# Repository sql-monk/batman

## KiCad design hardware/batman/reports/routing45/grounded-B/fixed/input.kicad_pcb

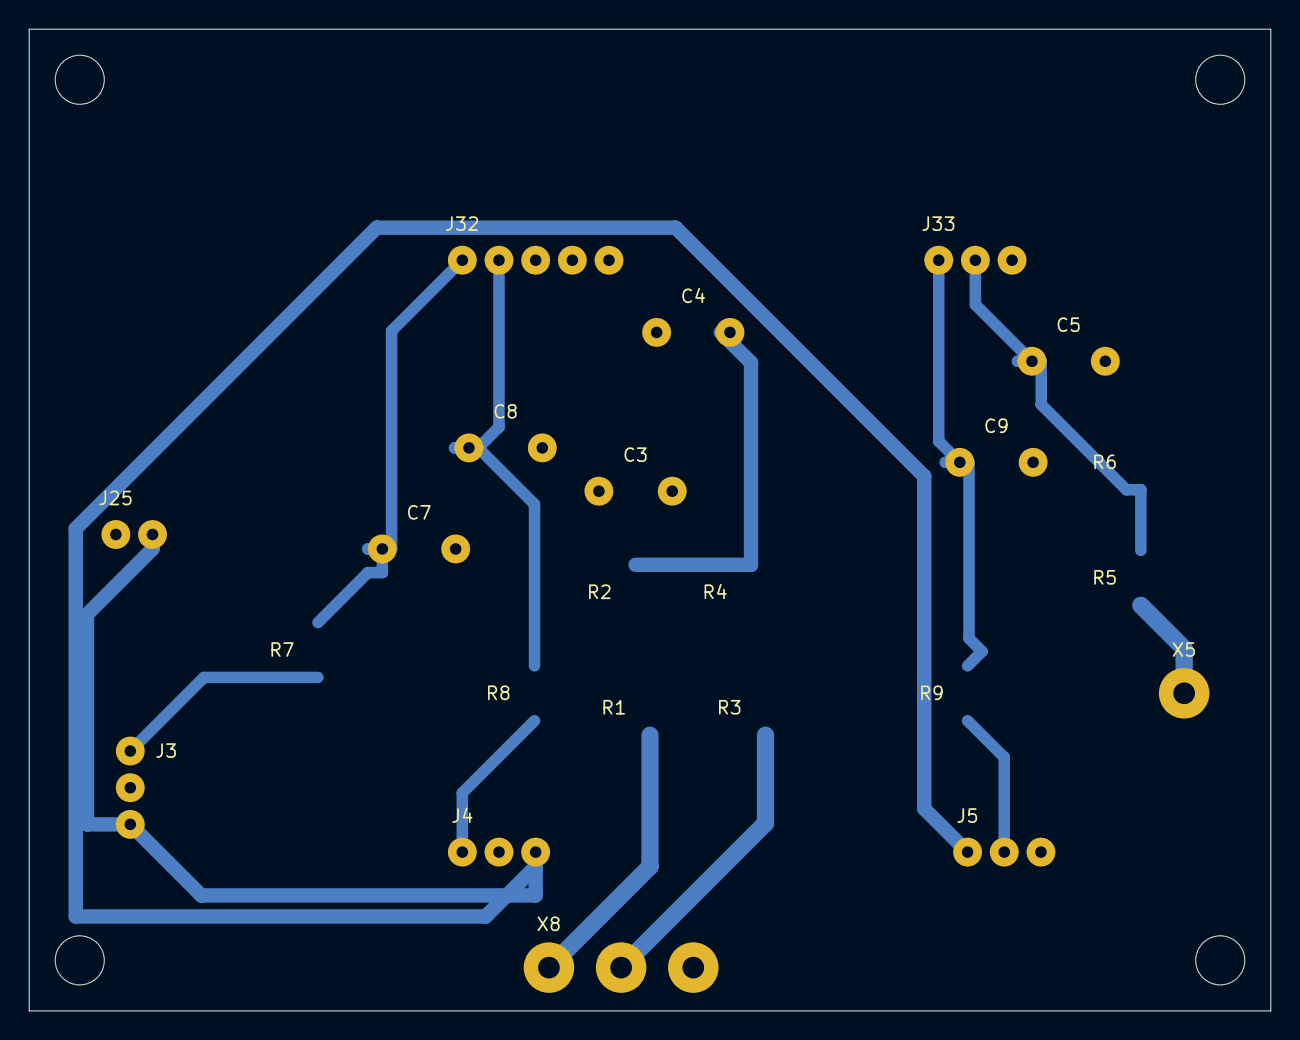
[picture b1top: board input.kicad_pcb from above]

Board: 2 copper layers, 86.0 x 68.0 mm, 27 parts (0 on the bottom side), 14 nets.

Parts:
C3: 100n_50V; LUT_C3
C4: 100n_50V; LUT_C4
C5: 100n_50V; LUT_C5
C7: 1u_16V; LUT_C7
C8: 1u_16V; LUT_C8
C9: 1u_16V; LUT_C9
HB1, HB2, HB3, HB4: M3_NPTH_3.4; Mount_M3
J3: ACS1_3WIRE; LUT_J3
J4: ACS2_3WIRE; LUT_J4
J5: ACS3_3WIRE; LUT_J5
J25: LINK_GND_+3V3_SENS; LUT_J25
J32: LINK_I_B1_I_B2_U_B1_U_B2_GND; LUT_J32
J33: LINK_I_LOAD_U_LOAD_GND; LUT_J33
R1: 100k_1%; LUT_R1
R2: 10k_1%; LUT_R2
R3: 100k_1%; LUT_R3
R4: 10k_1%; LUT_R4
R5: 100k_1%; LUT_R5
R6: 4.7k_1%; LUT_R6
R7: 1k; LUT_R7
R8: 1k; LUT_R8
R9: 1k; LUT_R9
X5: U_LOAD_SENSE; LUT_X5
X8: BAT_SENSE_FROM_D; LUT_X8

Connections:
+3V3_SENS: J3.3, J4.3, J5.1, J25.2
B1: R1.1, X8.1
B2: R3.1, X8.2
GND: C3.2, C4.2, C5.2, C7.2, C8.2, C9.2, J3.2, J4.2, J5.3, J25.1, J32.5, J33.3, R2.2, R4.2, R6.2, X8.3
I_B1: C7.1, J32.1, R7.2
I_B2: C8.1, J32.2, R8.2
I_LOAD: C9.1, J33.1, R9.2
I_RAW1: J3.1, R7.1
I_RAW2: J4.1, R8.1
I_RAW3: J5.2, R9.1
LOAD+: R5.1, X5.1
U_B1: C3.1, J32.3, R1.2, R2.1
U_B2: C4.1, J32.4, R3.2, R4.1
U_LOAD: C5.1, J33.2, R5.2, R6.1

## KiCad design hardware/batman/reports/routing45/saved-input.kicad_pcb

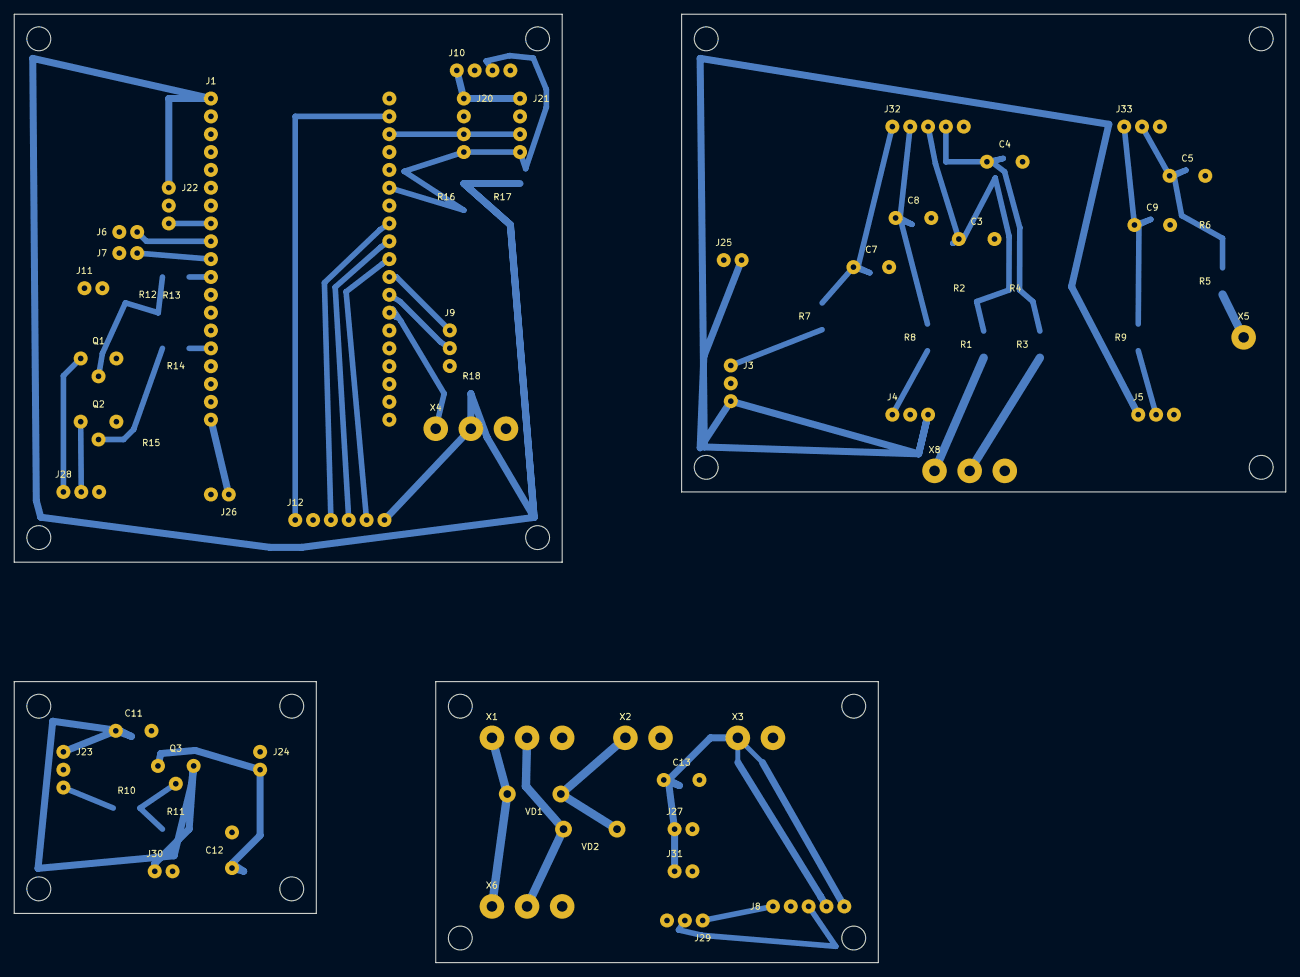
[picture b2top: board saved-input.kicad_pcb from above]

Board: 2 copper layers, 181.0 x 135.0 mm, 98 parts (0 on the bottom side), 39 nets.

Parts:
C3: 100n_50V; LUT_C3
C4: 100n_50V; LUT_C4
C5: 100n_50V; LUT_C5
C7: 1u_16V; LUT_C7
C8: 1u_16V; LUT_C8
C9: 1u_16V; LUT_C9
C11: 100n_16V; LUT_C11
C12: 100n_16V; LUT_C12
C13: 100n_16V; LUT_C13
HA1, HA2, HA3, HA4: M3_NPTH_3.4; Mount_M3
HB1, HB2, HB3, HB4: M3_NPTH_3.4; Mount_M3
HC1, HC2, HC3, HC4: M3_NPTH_3.4; Mount_M3
HD1, HD2, HD3, HD4: M3_NPTH_3.4; Mount_M3
J1: DevKitC_38_socket_mMCU; LUT_J1
J3: ACS1_3WIRE; LUT_J3
J4: ACS2_3WIRE; LUT_J4
J5: ACS3_3WIRE; LUT_J5
J6: SW1_GND_ON; LUT_J6
J7: SW2_GND_ON; LUT_J7
J8: RELAY; LUT_J8
J9: DPS_UART; LUT_J9
J10: OLED_I2C; LUT_J10
J11: BUTTON; LUT_J11
J12: SPI; LUT_J12
J20: LINK_+3V3_GND_SCL_SDA; LUT_J20
J21: LINK_+3V3_GND_SCL_SDA; LUT_J21
J22: LINK_+3V3_GND_SENS_PWR; LUT_J22
J23: LINK_+3V3_GND_SENS_PWR; LUT_J23
J24: LINK_GND_+3V3_SENS; LUT_J24
J25: LINK_GND_+3V3_SENS; LUT_J25
J26: LINK_+5V_GND; LUT_J26
J27: LINK_+5V_GND; LUT_J27
J28: LINK_RELAY_IN1_RELAY_IN2_GND; LUT_J28
J29: LINK_RELAY_IN1_RELAY_IN2_GND; LUT_J29
J30: LINK_+3V3_GND; LUT_J30
J31: LINK_+5V_GND; LUT_J31
J32: LINK_I_B1_I_B2_U_B1_U_B2_GND; LUT_J32
J33: LINK_I_LOAD_U_LOAD_GND; LUT_J33
NT1: COPPER_STAR_AT_X3; LUT_NT1
Q1: BC547_CBE; LUT_Q1
Q2: BC547_CBE; LUT_Q2
Q3: BC557_CBE; LUT_Q3
R1: 100k_1%; LUT_R1
R2: 10k_1%; LUT_R2
R3: 100k_1%; LUT_R3
R4: 10k_1%; LUT_R4
R5: 100k_1%; LUT_R5
R6: 4.7k_1%; LUT_R6
R7: 1k; LUT_R7
R8: 1k; LUT_R8
R9: 1k; LUT_R9
R10: 4.7k; LUT_R10
R11: 10k; LUT_R11
R12: 1k; LUT_R12
R13: 10k; LUT_R13
R14: 1k; LUT_R14
R15: 10k; LUT_R15
R16: 4.7k; LUT_R16
R17: 4.7k; LUT_R17
R18: 4.7k; LUT_R18
VD1: 1N5819; LUT_VD1
VD2: 1N5819; LUT_VD2
WA1: INSULATED_WIRE; LUT_WA1
WA2: INSULATED_WIRE; LUT_WA2
WA3: INSULATED_WIRE; LUT_WA3
WA4: INSULATED_WIRE; LUT_WA4
WC2_1: EXTERNAL_CABLE_NOT_PCB; LUT_WC2_1
WC2_2: EXTERNAL_CABLE_NOT_PCB; LUT_WC2_2
WC2_3: EXTERNAL_CABLE_NOT_PCB; LUT_WC2_3
WC3_1: EXTERNAL_CABLE_NOT_PCB; LUT_WC3_1
WC3_2: EXTERNAL_CABLE_NOT_PCB; LUT_WC3_2
WC4_1: EXTERNAL_CABLE_NOT_PCB; LUT_WC4_1
WC4_2: EXTERNAL_CABLE_NOT_PCB; LUT_WC4_2
WC5_1: EXTERNAL_CABLE_NOT_PCB; LUT_WC5_1
WC5_2: EXTERNAL_CABLE_NOT_PCB; LUT_WC5_2
WC5_3: EXTERNAL_CABLE_NOT_PCB; LUT_WC5_3
WC6_1: EXTERNAL_CABLE_NOT_PCB; LUT_WC6_1
WC6_2: EXTERNAL_CABLE_NOT_PCB; LUT_WC6_2
WC6_3: EXTERNAL_CABLE_NOT_PCB; LUT_WC6_3
X1: B1_B2_GND; LUT_X1
X2: VIN_DC_GND; LUT_X2
X3: 5V_GND; LUT_X3
X4: DS18B20; LUT_X4
X5: U_LOAD_SENSE; LUT_X5
X6: BAT_SENSE_TO_B; LUT_X6
X8: BAT_SENSE_FROM_D; LUT_X8

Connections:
+3V3: C11.1, J1.1, J10.1, J12.6, J20.1, J21.1, J22.1, J23.1, J30.1, Q3.3, R11.2, R16.2, R17.2, R18.2, WA1.1, WC2_1.1, X4.2
+3V3_SENS: C12.1, J3.3, J4.3, J5.1, J24.2, J25.2, Q3.1, WC3_2.1
+5V: C13.1, J1.19, J26.1, J27.1, J31.1, NT1.1, WC4_1.1, X3.1
+5V_RELAY_COIL: J8.5, NT1.3
+5V_RELAY_VCC: J8.4, NT1.2
B1: R1.1, VD1.2, WC6_1.1, X1.1, X6.1, X8.1
B2: R3.1, VD2.2, WC6_2.1, X1.2, X6.2, X8.2
BASE1: Q1.2, R12.2, R13.1
BASE2: Q2.2, R14.2, R15.1
BASE3: Q3.2, R10.2, R11.1
BTN: J1.7, J11.2, WA2.1
CS: J1.29, J12.5
DPS_RX: J1.31, J9.2
DPS_TX: J1.30, J9.1
GND: C3.2, C4.2, C5.2, C7.2, C8.2, C9.2, C11.2, C12.2, C13.2, J1.14, J1.20, J1.26, J3.2, J4.2, J5.3, J6.1, J7.1, J8.2, J9.3, J10.4, J11.1, J12.2, J20.2, J21.2, J22.2, J23.2, J24.1, J25.1, J26.2, J27.2, J28.3, J29.3, J30.2, J31.2, J32.5, J33.3, Q1.3, Q2.3, R2.2, R4.2, R6.2, R13.2, R15.2, WC2_2.1, WC3_1.1, WC4_2.1, WC5_3.1, WC6_3.1, X1.3, X2.2, X3.2, X4.3, X6.3, X8.3
I_B1: C7.1, J32.1, R7.2
I_B2: C8.1, J32.2, R8.2
I_LOAD: C9.1, J33.1, R9.2
I_RAW1: J3.1, R7.1
I_RAW2: J4.1, R8.1
I_RAW3: J5.2, R9.1
K1: J1.11, R12.1
K2: J1.15, R14.1
LOAD+: R5.1, X5.1
MISO: J1.27, J12.3
MOSI: J1.21, J12.1
OW: J1.32, R18.1, X4.1
RELAY_IN1: J8.1, J28.1, J29.1, Q1.1, WC5_1.1
RELAY_IN2: J8.3, J28.2, J29.2, Q2.1, WC5_2.1
SCK: J1.28, J12.4
SCL: J1.22, J10.2, J20.3, J21.3, R17.1, WA3.1, WA4.1
SDA: J1.25, J10.3, J20.4, J21.4, R16.1
SENS_PWR: J1.8, J22.3, J23.3, R10.1, WC2_3.1
SW1_ON: J1.9, J6.2
SW2_ON: J1.10, J7.2
U_B1: C3.1, J32.3, R1.2, R2.1
U_B2: C4.1, J32.4, R3.2, R4.1
U_LOAD: C5.1, J33.2, R5.2, R6.1
VIN_DC: VD1.1, VD2.1, X2.1

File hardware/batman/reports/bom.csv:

Reference,Documentation_alias,Value,Quantity,Location,Populate
J1,,DevKitC_38_socket_mMCU,1,A,yes
J2,,ADS1115_socket_mADC,1,A,yes
J3,,ACS1_3WIRE,1,A,yes
J4,,ACS2_3WIRE,1,A,yes
J5,,ACS3_3WIRE,1,A,yes
J6,,SW1_GND_ON,1,A,yes
J7,,SW2_GND_ON,1,A,yes
J8,,RELAY,1,A,yes
J9,,DPS_UART,1,A,yes
J10,,OLED_I2C,1,A,yes
J11,,BUTTON,1,A,yes
J12,,SPI,1,A,yes
X1,,B1_B2_GND,1,A,yes
X2,,VIN_DC_GND,1,A,yes
X3,,5V_GND,1,A,yes
X4,,DS18B20,1,A,yes
X5,,U_LOAD_SENSE,1,A,yes
NT1,,COPPER_STAR_AT_X3,1,A,copper only
VD1,,1N5819,1,A,yes
VD2,,1N5819,1,A,yes
R1,,100k_1%,1,A,yes
R2,,10k_1%,1,A,yes
C3,,100n_50V,1,A,yes
R3,,100k_1%,1,A,yes
R4,,10k_1%,1,A,yes
C4,,100n_50V,1,A,yes
R5,,100k_1%,1,A,yes
R6,,4.7k_1%,1,A,yes
C5,,100n_50V,1,A,yes
R7,,1k,1,A,yes
C7,,1u_16V,1,A,yes
R8,,1k,1,A,yes
C8,,1u_16V,1,A,yes
R9,,1k,1,A,yes
C9,,1u_16V,1,A,yes
C6,,100n_16V,1,A,yes
R10,,4.7k,1,A,yes
R11,,10k,1,A,yes
Q3,,BC557_CBE,1,A,yes
R12,,1k,1,A,yes
R13,,10k,1,A,yes
Q1,,BC547_CBE,1,A,yes
R14,,1k,1,A,yes
R15,,10k,1,A,yes
Q2,,BC547_CBE,1,A,yes
R16,,4.7k,1,A,yes
R17,,4.7k,1,A,yes
R18,,4.7k,1,A,yes
XLP1,XLP,LOAD_P06_P12_P13,1,external,yes
XGND1,XGND,GND_P24_P25_P26_P27_P28,1,external,yes
C1,,100u_50V_ALUMINIUM,1,external,yes
C2,,100n_50V,1,external,yes
D3,,1.5KE33A_DNP,1,external,DNP
XB1,,BAT1_PANEL,1,external,yes
F1,,ATO_15A,1,external,yes
mACS1,,ACS711EX_15.5A,1,external,yes
mSW1,,Pololu_2815_HP,1,external,yes
mDIO1,,XL74610,1,external,yes
XB2,,BAT2_PANEL,1,external,yes
F2,,ATO_15A,1,external,yes
mACS2,,ACS711EX_15.5A,1,external,yes
mSW2,,Pololu_2815_HP,1,external,yes
mDIO2,,XL74610,1,external,yes
mACS3,,ACS711EX_15.5A,1,external,yes
Fout1,Fout,ATO_15A,1,external,yes
XLOAD1,XLOAD,LOAD_PANEL,1,external,yes
XPSU1,XPSU,PSU_33V_10A_PANEL,1,external,yes
mDPS1,mDPS,DPS5015_9600_8N1_ADDR1,1,external,yes
Fchg1,Fchg,ATO_15A,1,external,yes
mDIO3,,XL74610,1,external,yes
mREL2,,FL_3FF_5V_10A_REMOVE_JUMPER,1,external,yes
mDC5,,LM2596_SET_5.0V_FIRST,1,external,yes
mOLED1,mOLED,SSD1306_0x3C,1,external,yes
T1,,DS18B20_PROBE,1,external,yes
T2,,DS18B20_PROBE,1,external,yes
SW1,,PANEL_BUTTON_NO,1,external,yes

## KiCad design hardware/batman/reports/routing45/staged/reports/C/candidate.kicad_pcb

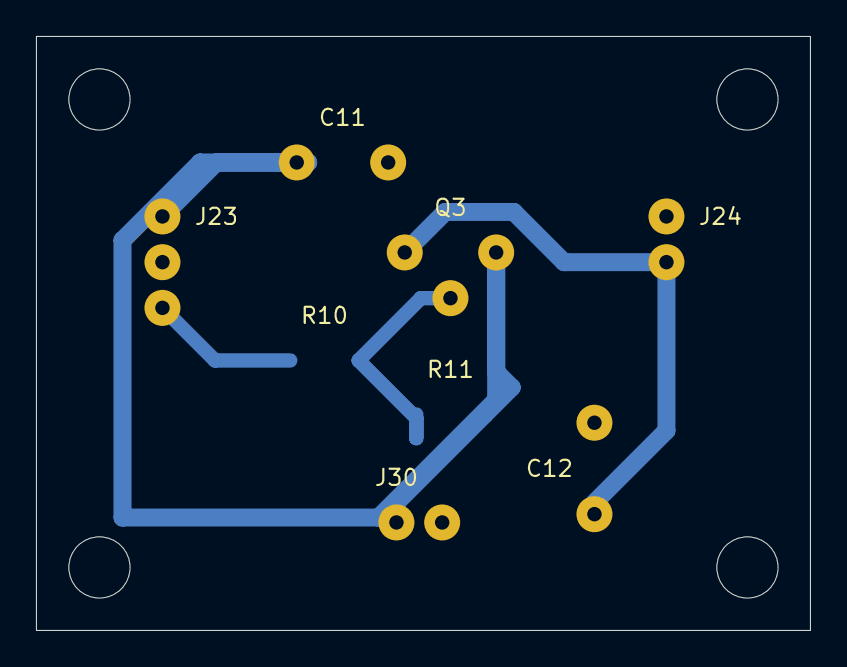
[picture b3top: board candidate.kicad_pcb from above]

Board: 2 copper layers, 43.0 x 33.0 mm, 12 parts (0 on the bottom side), 5 nets.

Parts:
C11: 100n_16V; LUT_C11
C12: 100n_16V; LUT_C12
HC1, HC2, HC3, HC4: M3_NPTH_3.4; Mount_M3
J23: LINK_+3V3_GND_SENS_PWR; LUT_J23
J24: LINK_GND_+3V3_SENS; LUT_J24
J30: LINK_+3V3_GND; LUT_J30
Q3: BC557_CBE; LUT_Q3
R10: 4.7k; LUT_R10
R11: 10k; LUT_R11

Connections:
+3V3: C11.1, J23.1, J30.1, Q3.3, R11.2
+3V3_SENS: C12.1, J24.2, Q3.1
BASE3: Q3.2, R10.2, R11.1
GND: C11.2, C12.2, J23.2, J24.1, J30.2
SENS_PWR: J23.3, R10.1

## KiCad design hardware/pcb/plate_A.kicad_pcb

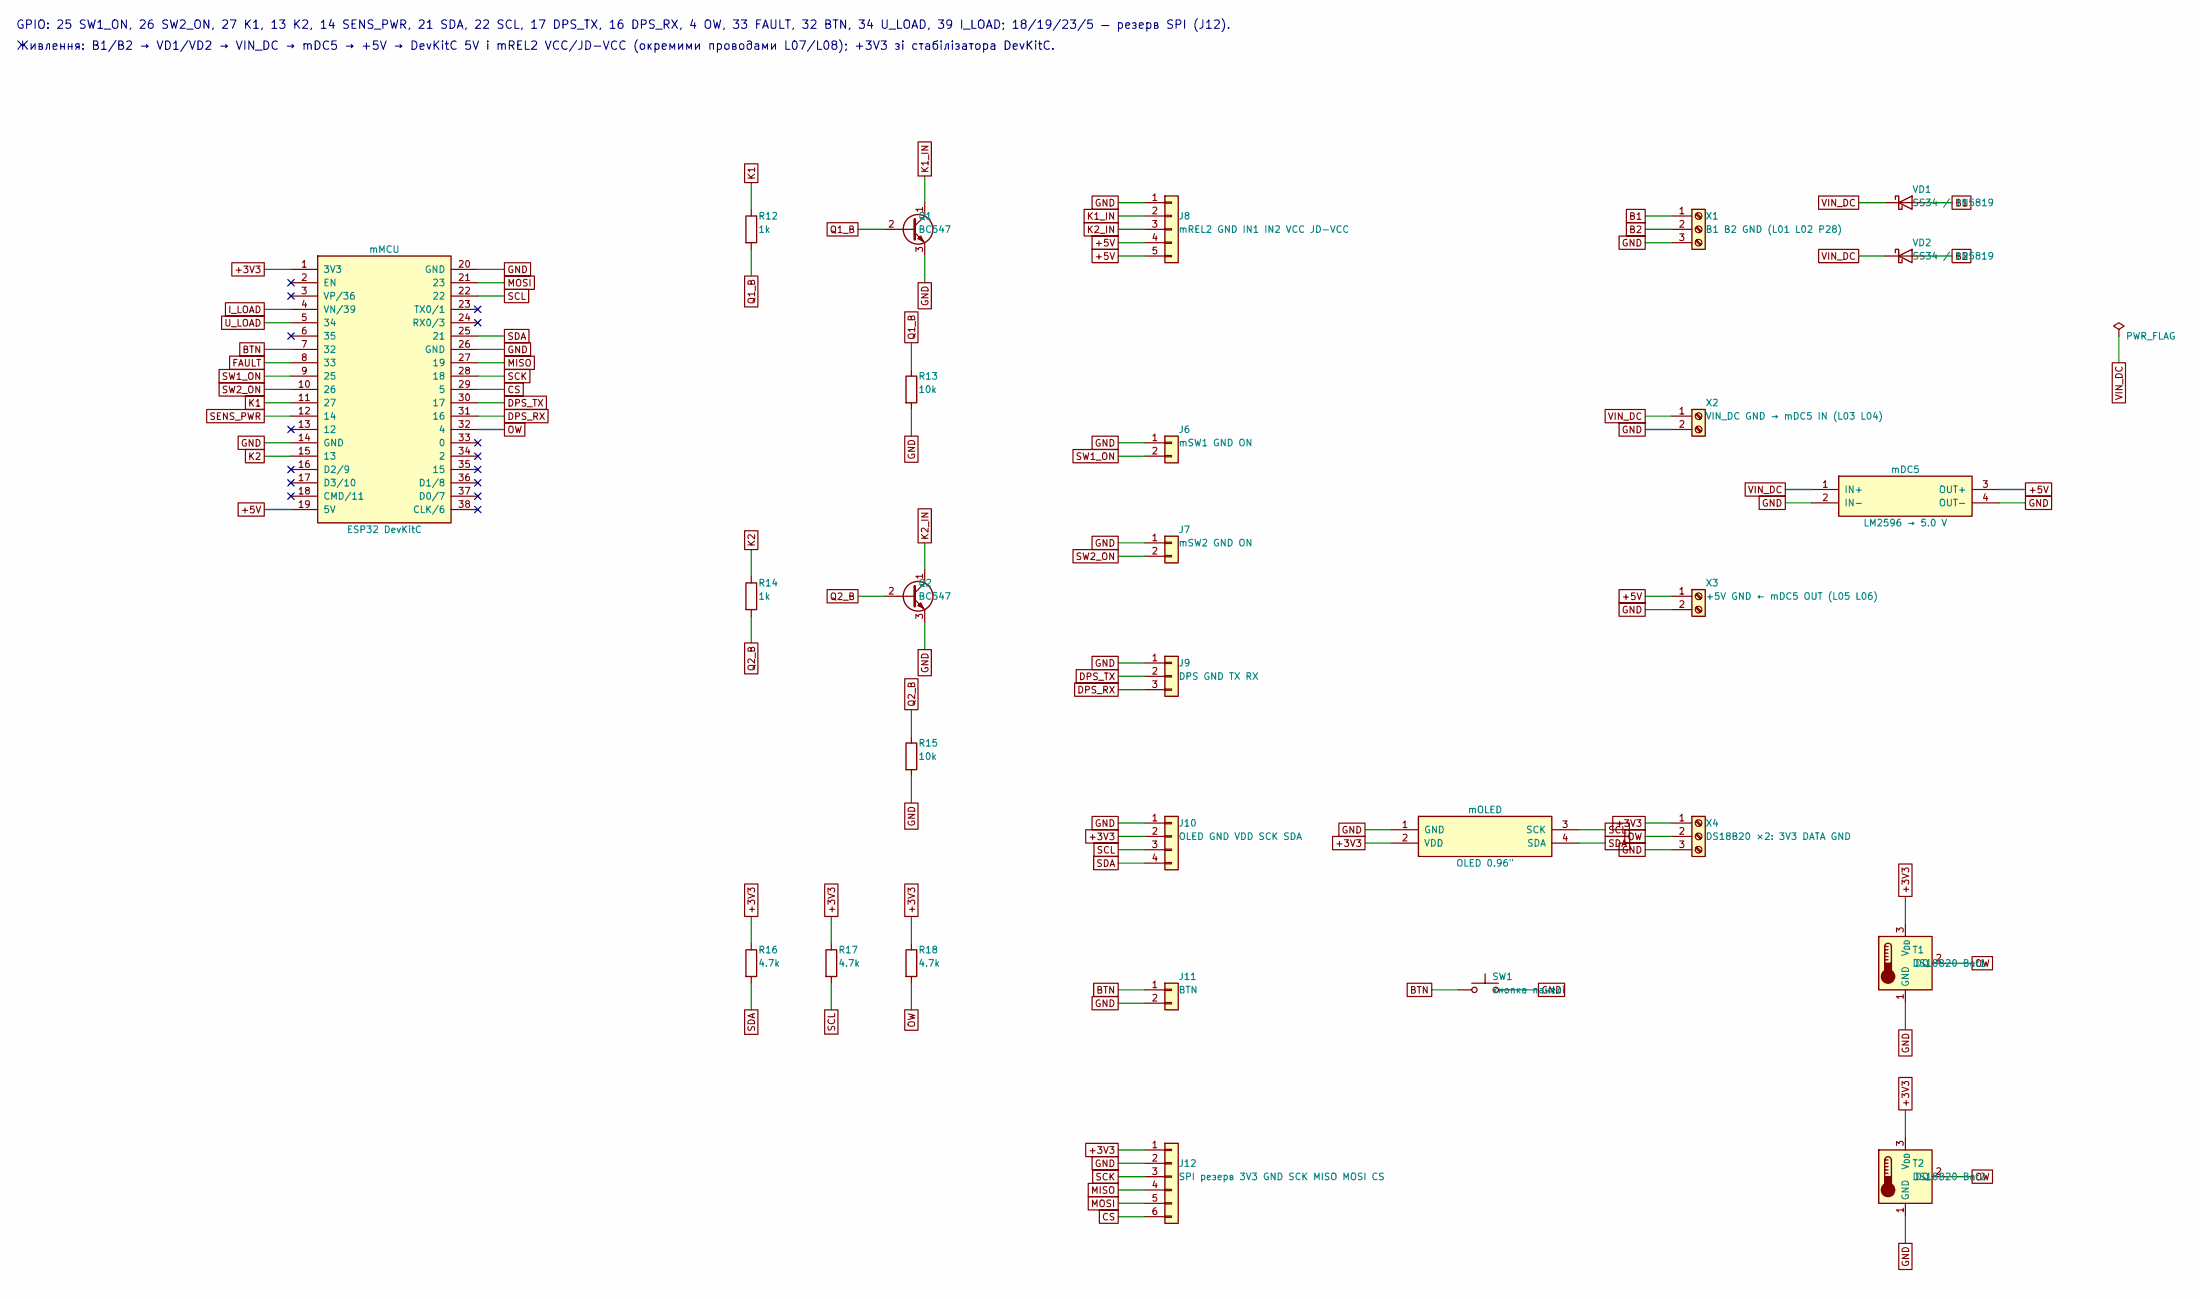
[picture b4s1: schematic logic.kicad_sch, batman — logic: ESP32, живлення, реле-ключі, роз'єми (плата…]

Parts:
J6: mSW1 GND ON; PinHeader_1x02_P2.54mm_Vertical
J7: mSW2 GND ON; PinHeader_1x02_P2.54mm_Vertical
J8: mREL2 GND IN1 IN2 VCC JD-VCC; PinHeader_1x05_P2.54mm_Vertical
J9: DPS GND TX RX; PinHeader_1x03_P2.54mm_Vertical
J10: OLED GND VDD SCK SDA; PinHeader_1x04_P2.54mm_Vertical
J11: BTN; PinHeader_1x02_P2.54mm_Vertical
J12: SPI резерв 3V3 GND SCK MISO MOSI CS; PinHeader_1x06_P2.54mm_Vertical
Q1, Q2: BC547; TO-92_Inline
R12, R14: 1k; R_1206_3216Metric
R13, R15: 10k; R_1206_3216Metric
R16, R17, R18: 4.7k; R_1206_3216Metric
SW1: кнопка панелі; SW_PUSH_6mm
T1: DS18B20 Bat1
T2: DS18B20 Bat2
VD1, VD2: SS34 / 1N5819; D_DO-41_SOD81_P10.16mm_Horizontal
X1: B1 B2 GND (L01 L02 P28); TerminalBlock_MaiXu_MX126-5.0-03P_1x03_P5.00mm
X2: VIN_DC GND → mDC5 IN (L03 L04); TerminalBlock_MaiXu_MX126-5.0-02P_1x02_P5.00mm
X3: +5V GND ← mDC5 OUT (L05 L06); TerminalBlock_MaiXu_MX126-5.0-02P_1x02_P5.00mm
X4: DS18B20 ×2: 3V3 DATA GND; TerminalBlock_MaiXu_MX126-5.0-03P_1x03_P5.00mm
mDC5: LM2596 → 5.0 V
mMCU: ESP32 DevKitC; ESP32_DevKitC_38_Socket
mOLED: OLED 0.96"

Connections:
+3V3: J10.2, J12.1, R16.1, R17.1, R18.1, T1.3 (V_{DD}), T2.3 (V_{DD}), X4.1, mMCU.1 (3V3), mOLED.2 (VDD); also elsewhere on the board
+5V: J8.4, J8.5, X3.1, mDC5.3 (OUT+), mMCU.19 (5V)
B1: VD1.2 (A), X1.1; also elsewhere on the board
B2: VD2.2 (A), X1.2; also elsewhere on the board
BTN: J11.1, SW1.1, mMCU.7 (32)
CS: J12.6, mMCU.29 (5)
DPS_RX: J9.3, mMCU.31 (16)
DPS_TX: J9.2, mMCU.30 (17)
FAULT: mMCU.8 (33); also elsewhere on the board
GND: J6.1, J7.1, J8.1, J9.1, J10.1, J11.2, J12.2, Q1.3 (E), Q2.3 (E), R13.2, R15.2, SW1.2, T1.1 (GND), T2.1 (GND), X1.3, X2.2, X3.2, X4.3, mDC5.2 (IN-), mDC5.4 (OUT-), mMCU.14 (GND), mMCU.20 (GND), mMCU.26 (GND), mOLED.1 (GND); also elsewhere on the board
I_LOAD: mMCU.4 (VN/39); also elsewhere on the board
K1: R12.1, mMCU.11 (27)
K1_IN: J8.2, Q1.1 (C)
K2: R14.1, mMCU.15 (13)
K2_IN: J8.3, Q2.1 (C)
MISO: J12.4, mMCU.27 (19)
MOSI: J12.5, mMCU.21 (23)
OW: R18.2, T1.2 (DQ), T2.2 (DQ), X4.2, mMCU.32 (4)
Q1_B: Q1.2 (B), R12.2, R13.1
Q2_B: Q2.2 (B), R14.2, R15.1
SCK: J12.3, mMCU.28 (18)
SCL: J10.3, R17.2, mMCU.22, mOLED.3 (SCK); also elsewhere on the board
SDA: J10.4, R16.2, mMCU.25 (21), mOLED.4 (SDA); also elsewhere on the board
SENS_PWR: mMCU.12 (14); also elsewhere on the board
SW1_ON: J6.2, mMCU.9 (25)
SW2_ON: J7.2, mMCU.10 (26)
U_LOAD: mMCU.5 (34); also elsewhere on the board
VIN_DC: VD1.1 (K), VD2.1 (K), X2.1, mDC5.1 (IN+)

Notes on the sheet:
GPIO: 25 SW1_ON, 26 SW2_ON, 27 K1, 13 K2, 14 SENS_PWR, 21 SDA, 22 SCL, 17 DPS_TX, 16 DPS_RX, 4 OW, 33 FAULT, 32 BTN, 34 U_LOAD, 39 I_LOAD; 18/19/23/5 — резерв SPI (J12).
Живлення: B1/B2 → VD1/VD2 → VIN_DC → mDC5 → +5V → DevKitC 5V і mREL2 VCC/JD-VCC (окремими проводами L07/L08); +3V3 зі стабілізатора DevKitC.

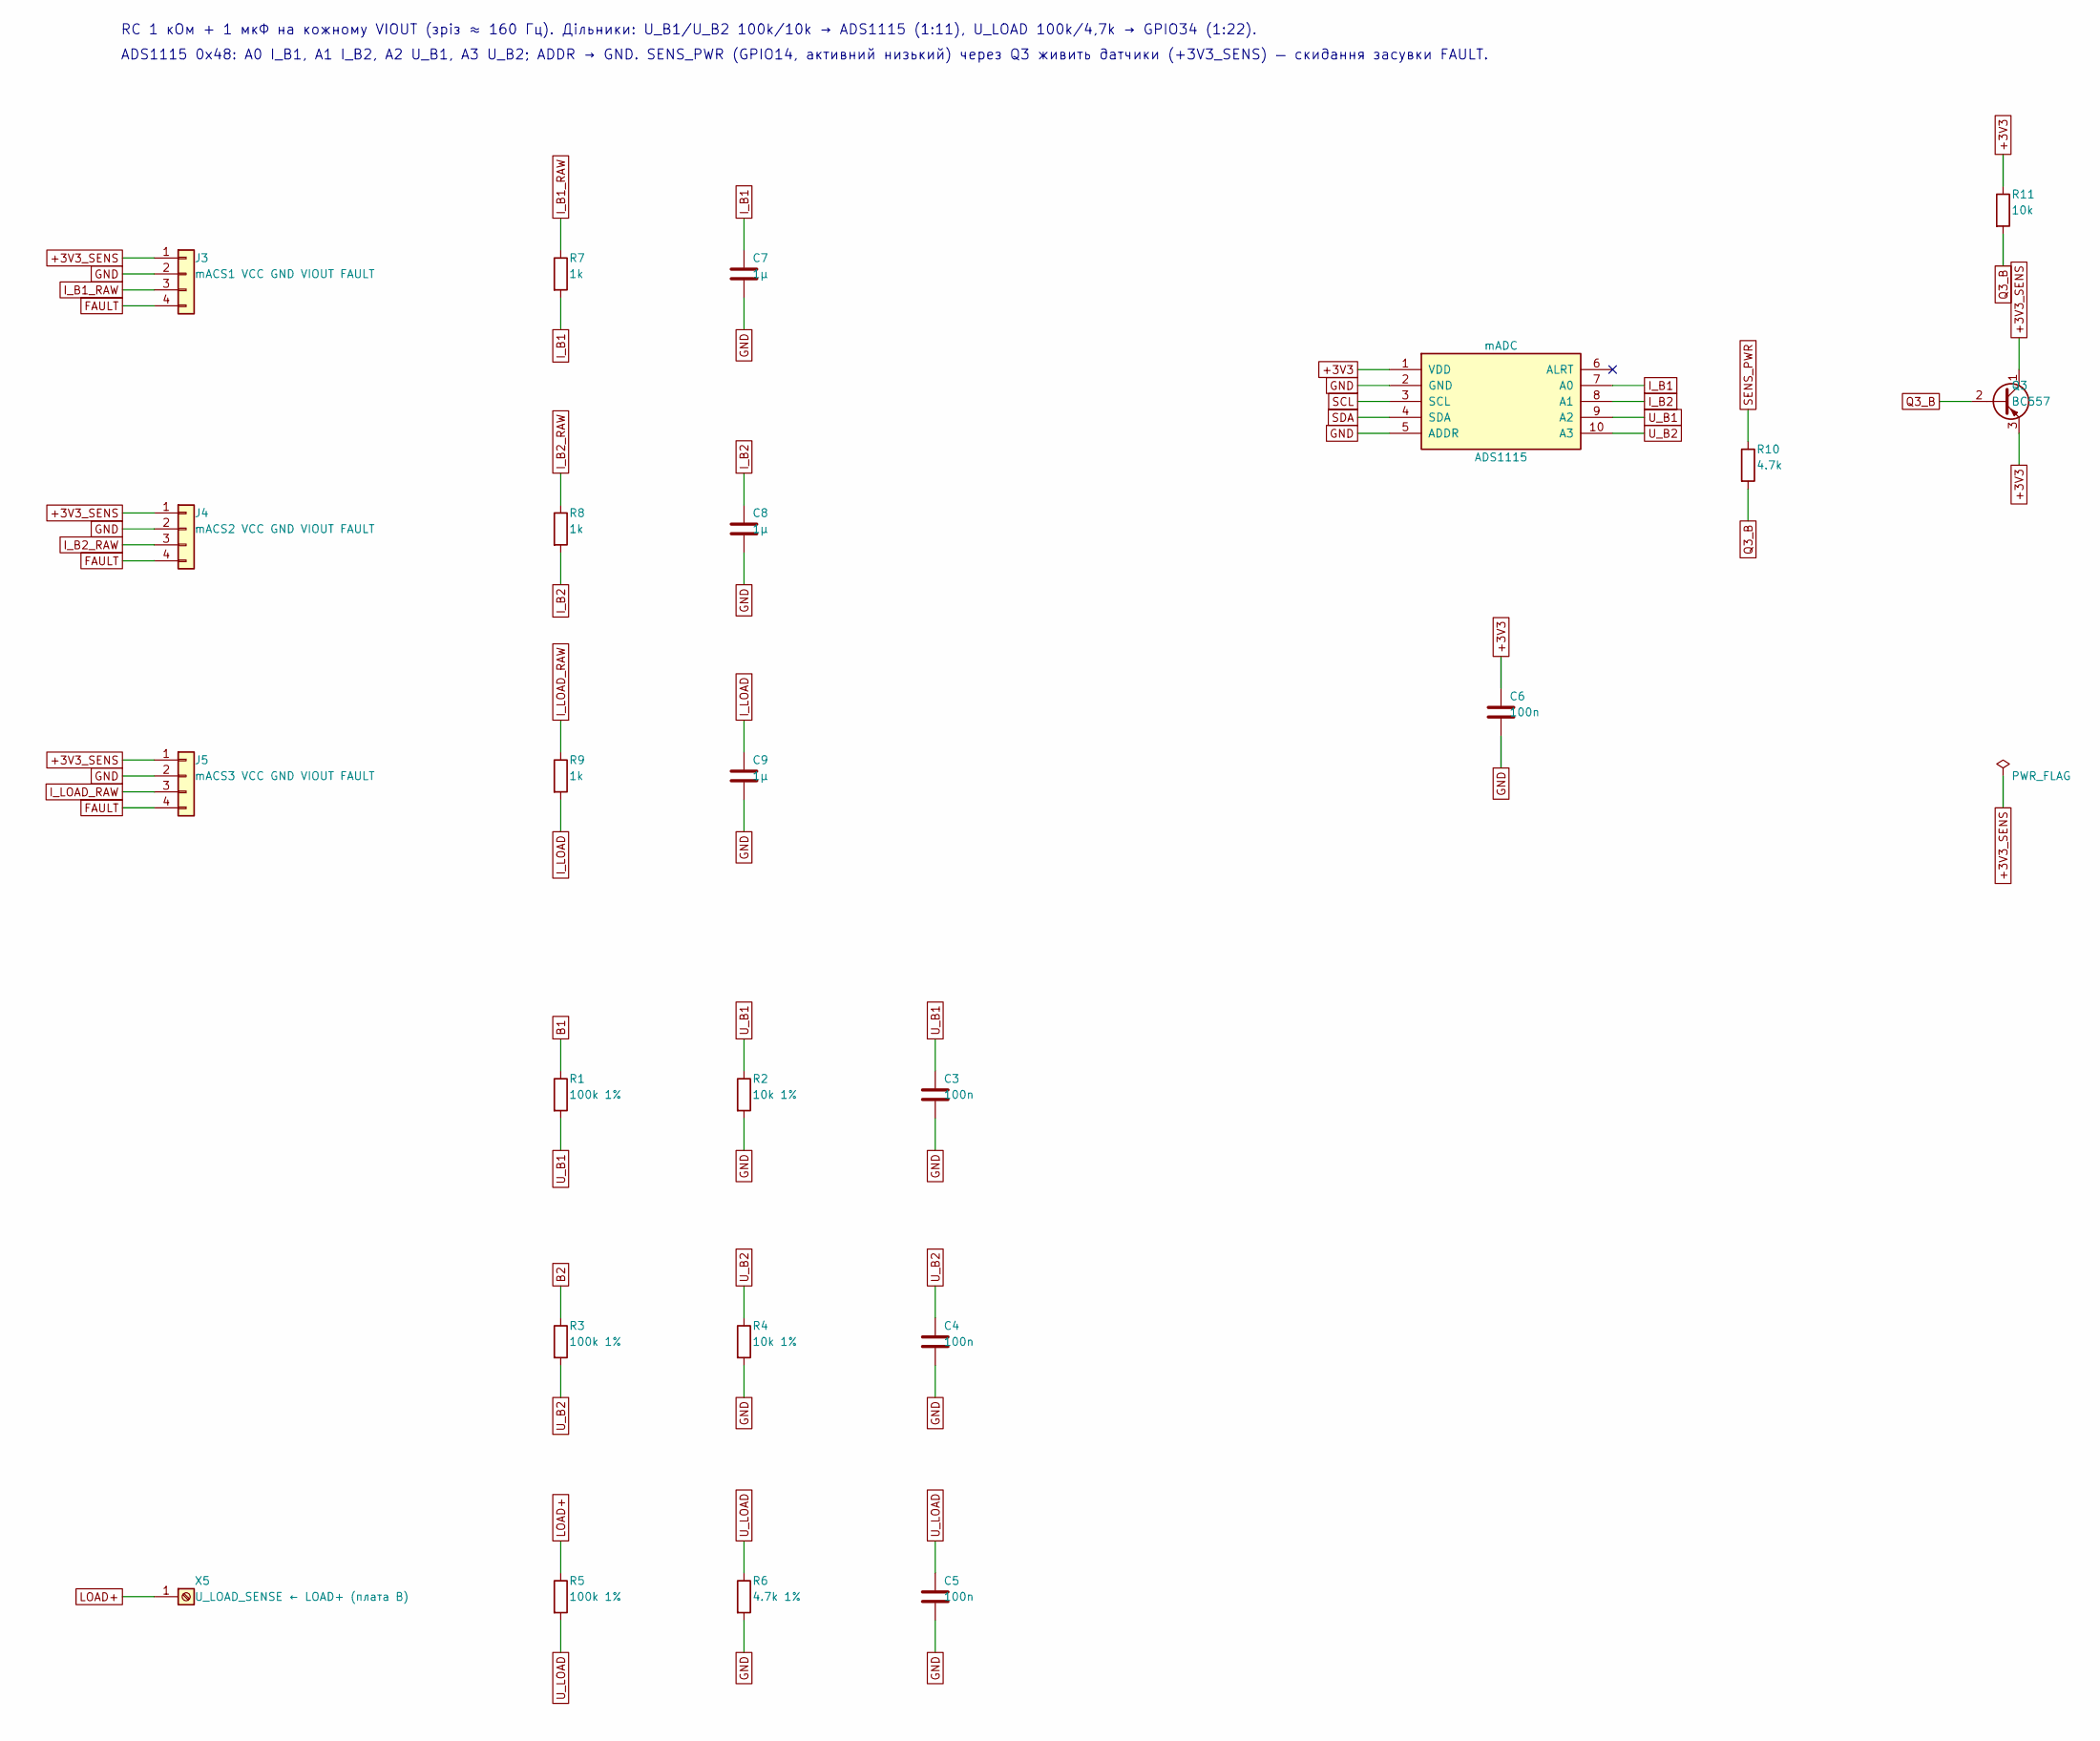
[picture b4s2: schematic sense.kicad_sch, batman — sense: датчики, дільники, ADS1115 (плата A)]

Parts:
C3, C4, C5, C6: 100n; C_Disc_D5.0mm_W2.5mm_P5.00mm
C7, C8, C9: 1µ; C_Disc_D5.0mm_W2.5mm_P5.00mm
J3: mACS1 VCC GND VIOUT FAULT; PinHeader_1x04_P2.54mm_Vertical
J4: mACS2 VCC GND VIOUT FAULT; PinHeader_1x04_P2.54mm_Vertical
J5: mACS3 VCC GND VIOUT FAULT; PinHeader_1x04_P2.54mm_Vertical
Q3: BC557; TO-92_Inline
R1, R3, R5: 100k 1%; R_1206_3216Metric
R2, R4: 10k 1%; R_1206_3216Metric
R6: 4.7k 1%; R_1206_3216Metric
R7, R8, R9: 1k; R_1206_3216Metric
R10: 4.7k; R_1206_3216Metric
R11: 10k; R_1206_3216Metric
X5: U_LOAD_SENSE ← LOAD+ (плата B); TerminalBlock_MaiXu_MX126-5.0-02P_1x02_P5.00mm
mADC: ADS1115; PinSocket_1x10_P2.54mm_Vertical

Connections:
+3V3: C6.1, Q3.3 (E), R11.1, mADC.1 (VDD); also elsewhere on the board
+3V3_SENS: J3.1, J4.1, J5.1, Q3.1 (C)
B1: R1.1; also elsewhere on the board
B2: R3.1; also elsewhere on the board
FAULT: J3.4, J4.4, J5.4; also elsewhere on the board
GND: C3.2, C4.2, C5.2, C6.2, C7.2, C8.2, C9.2, J3.2, J4.2, J5.2, R2.2, R4.2, R6.2, mADC.2 (GND), mADC.5 (ADDR); also elsewhere on the board
I_B1: C7.1, R7.2, mADC.7 (A0)
I_B1_RAW: J3.3, R7.1
I_B2: C8.1, R8.2, mADC.8 (A1)
I_B2_RAW: J4.3, R8.1
I_LOAD: C9.1, R9.2; also elsewhere on the board
I_LOAD_RAW: J5.3, R9.1
LOAD+: R5.1, X5.1
Q3_B: Q3.2 (B), R10.2, R11.2
SCL: mADC.3 (SCL); also elsewhere on the board
SDA: mADC.4 (SDA); also elsewhere on the board
SENS_PWR: R10.1; also elsewhere on the board
U_B1: C3.1, R1.2, R2.1, mADC.9 (A2)
U_B2: C4.1, R3.2, R4.1, mADC.10 (A3)
U_LOAD: C5.1, R5.2, R6.1; also elsewhere on the board

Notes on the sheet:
RC 1 кОм + 1 мкФ на кожному VIOUT (зріз ≈ 160 Гц). Дільники: U_B1/U_B2 100k/10k → ADS1115 (1:11), U_LOAD 100k/4,7k → GPIO34 (1:22).
ADS1115 0x48: A0 I_B1, A1 I_B2, A2 U_B1, A3 U_B2; ADDR → GND. SENS_PWR (GPIO14, активний низький) через Q3 живить датчики (+3V3_SENS) — скидання засувки FAULT.

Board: 2 copper layers, 51 parts (0 on the bottom side), 38 nets, no tracks yet.

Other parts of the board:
H1, H2, H3, H4: MountingHole_3.2mm_M3
